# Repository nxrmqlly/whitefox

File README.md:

# whitefox :: an RP2350B devboard
> 💥 very chonky!

## What's this? ooh shiny.

whitefox is a Raspberry Pi RP2350B based **devboard** with *47 exposed GPIO, a 3x3 neopixel grid, a charging circuit and a MicroSD card reader* onboard!
Some may even say that it is *batteries included* but sorry we don't include batteries :(

## Why?

I wanted to have a go at making a devboard so I initially thought of using the RP2040 Chip but that thing is old now and very overused so here
we are with the RP2040's successor, the RP2350! Most RP2350 boards (like the Raspberry Pi Pico *2*) use the QFN-60 layout on the RP2350A chip 
and I haven't really seen devboards use the RP2350B, which is a QFN-80 chip, meaning it exposes the full power of the RP2350 in a bigger die.

## The PCB

The Schematic is a combination of very many different projects and the official and amazing
[Hardware design with RP2350](https://pip-assets.raspberrypi.com/categories/1214-rp2350/documents/RP-008280-DS-1-hardware-design-with-rp2350.pdf)
The PCB is configured in a 4 layer stackup as follows (from the top): `SIG / GND / PWR / SIG` and includes copper pours on all layers except
the PWR layer (duh.)
Most components are SMD on top of the board, only the JST connector is through hole.

The PCB exposes two 2x16 standard 2.54 mm pitch header holes on both sides and an additional 1x3 2.54mm pitch connector as a debug header.

| What                                       | Image                                |
|--------------------------------------------|--------------------------------------|
| [PCB](./Docs/whitefox-pcb.pdf)             |              |
| [Schematic](./Docs/whitefox-schematic.pdf) |  |

The PCB and Schematic are available in a high quality PDFs in [Docs/](Docs/)

## 3D stuff
| <center>Front</center>             | <center>Back</center>            |
|------------------------------------|----------------------------------|
|  |  |

## The BOM

Lazy to type it here so...

The full BOM can be found at [BOM/bom.csv](./BOM/BOM.csv)!

## Why the name?

> There are 2 hard problems in computer science: cache invalidation, **naming things**, and off-by-1 errors.
>
> *-- Leon Bambrick*

yeah that should be enough for an explanation.

## How to build / use it IRL

1. Spend some \$\$\$ get parts from the [BOM](./BOM/BOM.csv)
2. Use the gerbers from [production/gerbers.zip](production/gerbers.zip) to fabricate a PCB.
3. With some elbow grease and reference from the schematic, get to soldering the tiny SMD components
4. You're done! Go crazy

Alternatively, you can preserve your sanity and [get a PCBA service instead.](https://jlcpcb.com)
1. Gerbers are at [production/gerbers.zip](production/gerbers.zip)
2. JLCPCB BOM (not project bom!!) is at [production/jlc_bom.csv](production/jlc_bom.csv)
3. Pick and Place (CPL) file is at [production/positions.csv](production/positions.csv)

## Credits where credits are due.

Grateful for:
- [euvalennn's RPBoard^2](https://github.com/euvalennn/rpboard-squared) for a lot of design inspiration and schematic help.
- [Fallout by hackclub](https://fallout.hackclub.com/) for giving me the oppourtunity and public brand assets!
- hackclub slack for the coolest people that helped out!

## License

The hardware (PCB) is licensed under `CERN Open Hardware Licence Version 2 - Strongly Reciprocal` which means, you're all-right to copy my work and use it in yours but you must disclose your source code and project files to opensource repositories if you include part of my work in yours. See [LICENSE](LICENSE).

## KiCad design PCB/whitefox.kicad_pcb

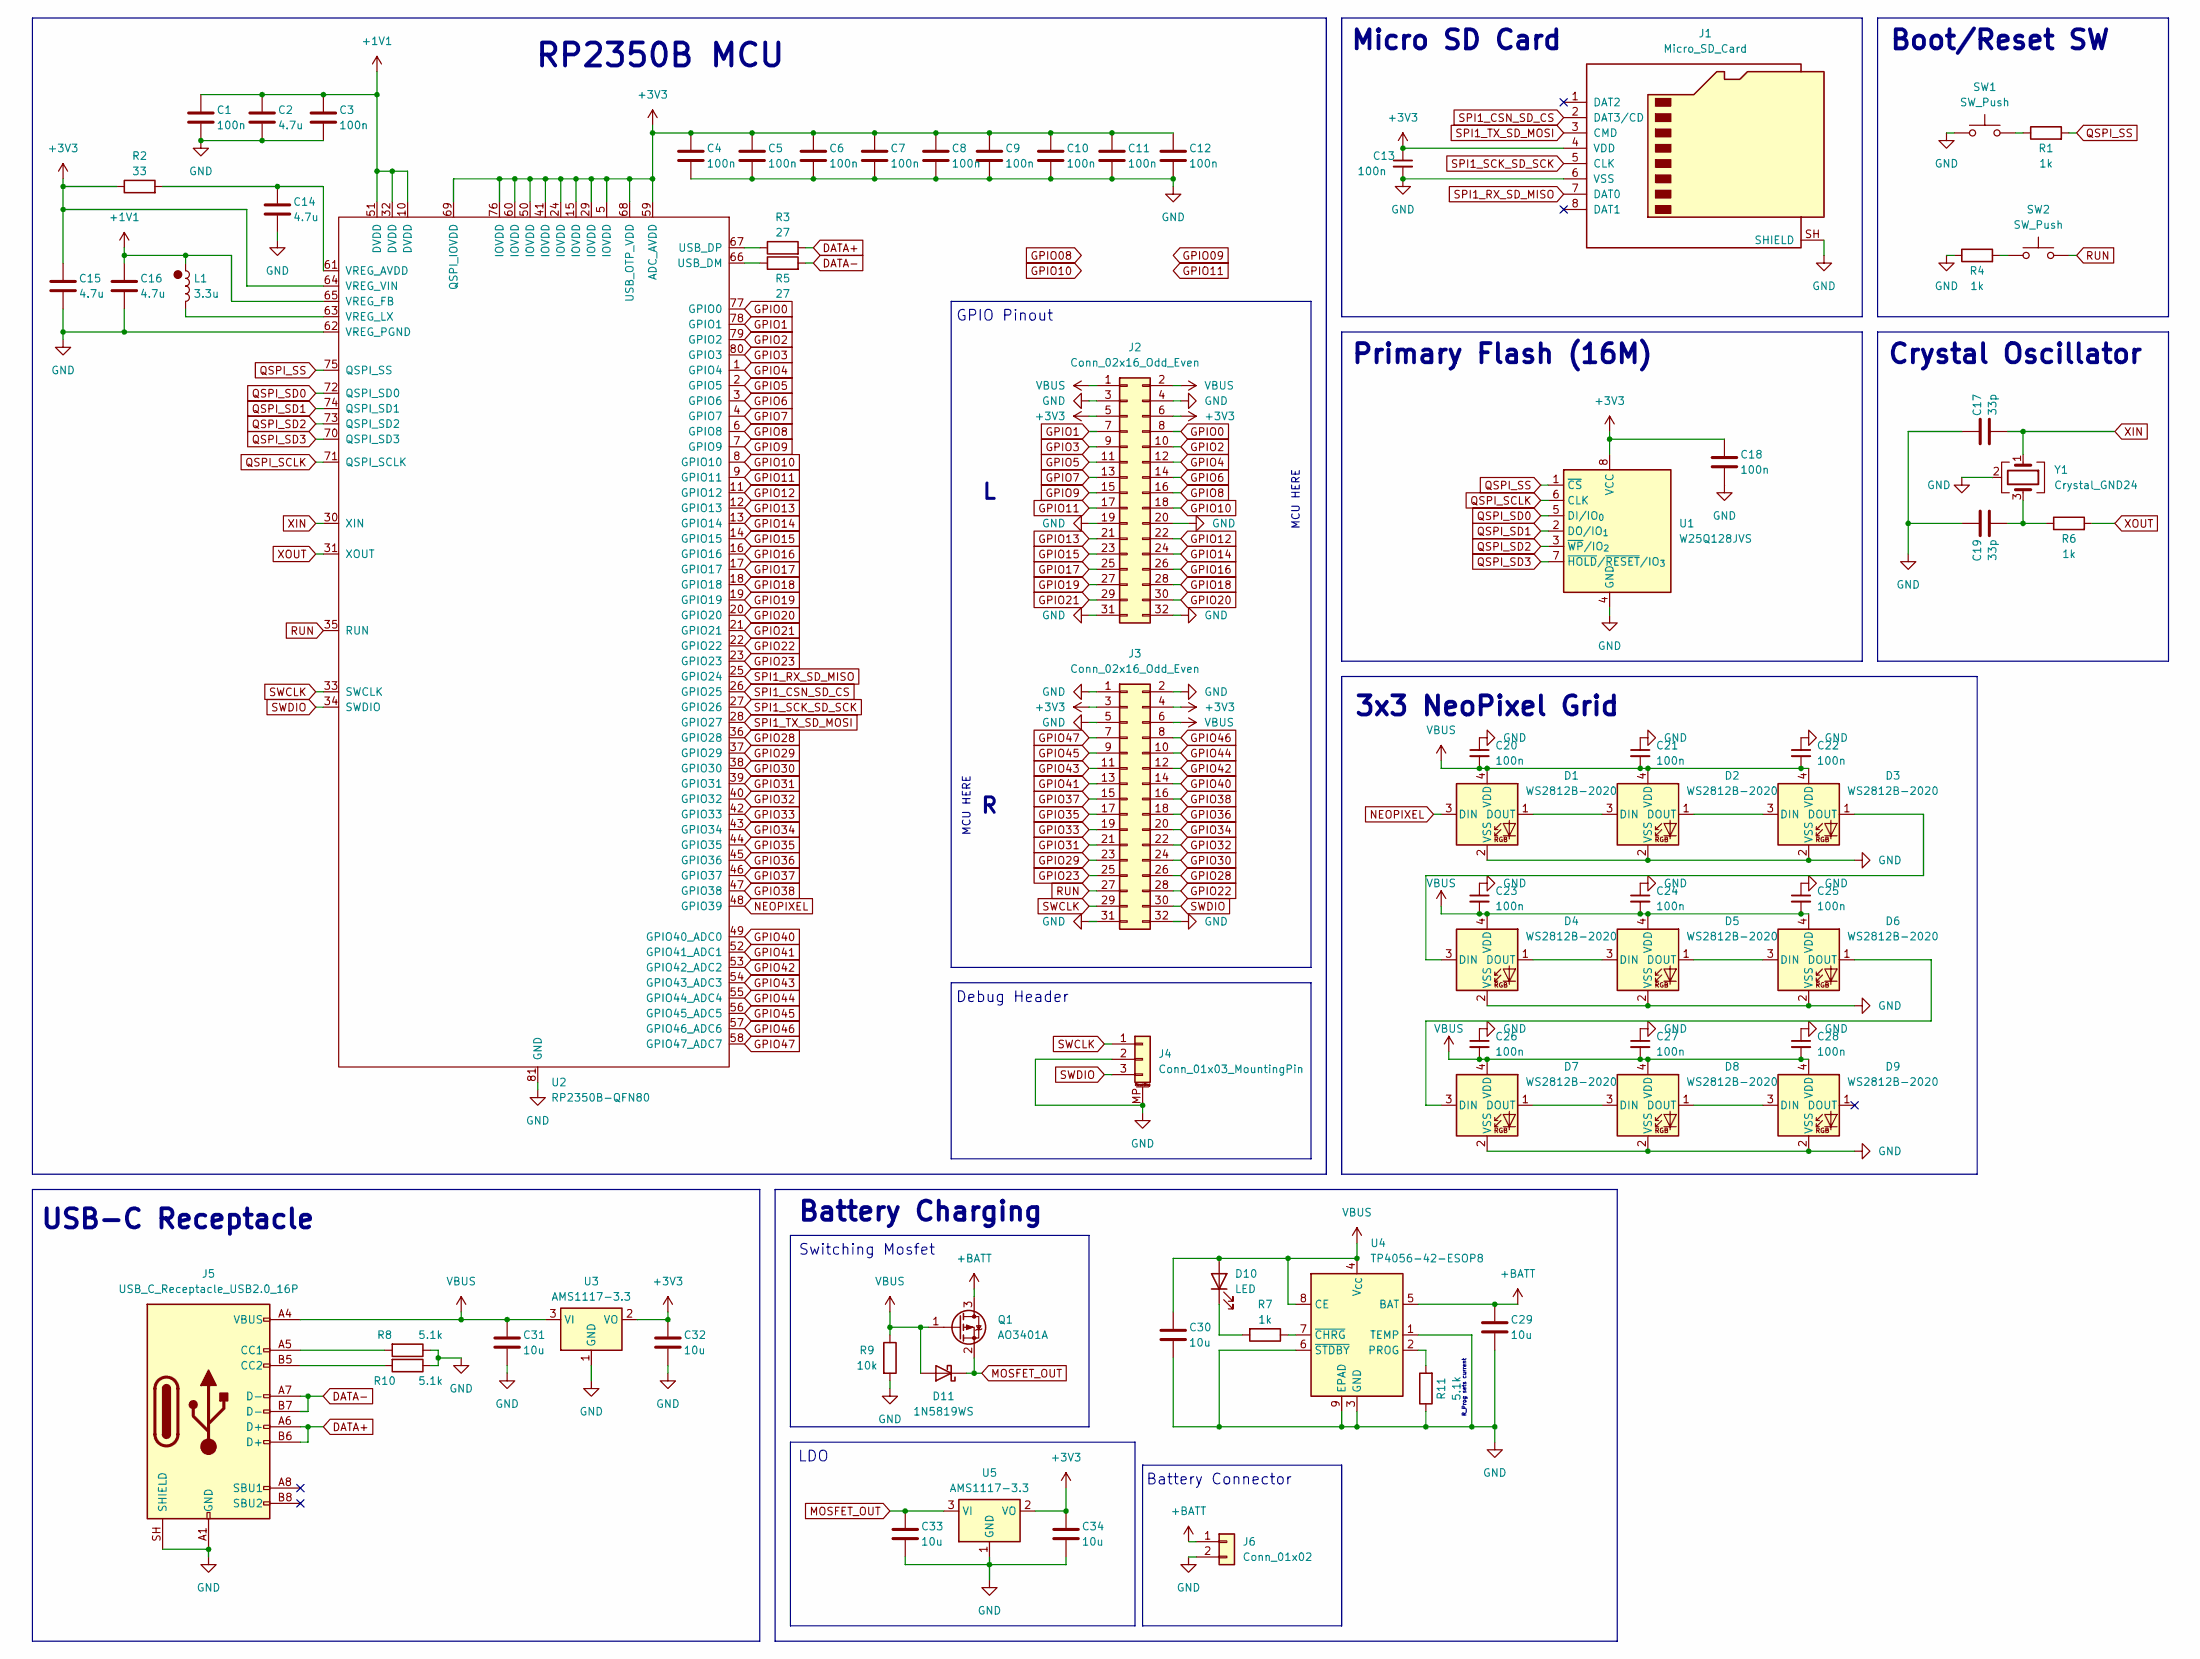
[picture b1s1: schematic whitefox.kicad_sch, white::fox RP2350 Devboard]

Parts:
C1, C3, C4, C5, C6, C7, C8, C9, C10, C11, C12, C13, C18, C20, C21, C22, C23, C24, C25, C26, C27, C28: 100n; C_0402_1005Metric
C2, C14, C15, C16: 4.7u; C_0402_1005Metric
C17, C19: 33p; C_0402_1005Metric
C29, C30, C31, C32, C33, C34: 10u; C_0402_1005Metric
D1, D2, D3, D4, D5, D6, D7, D8, D9: WS2812B-2020; LED_WS2812C-2020
D10: LED; LED_0603_1608Metric
D11: 1N5819WS; D_SOD-323
J1: Micro_SD_Card; TF-01A
J2, J3: Conn_02x16_Odd_Even; PinHeader_2x16_P2.54mm_Vertical
J4: Conn_01x03_MountingPin; PinHeader_1x03_P2.54mm_Vertical
J5: USB_C_Receptacle_USB2.0_16P; TYPE-C-31-M-12
J6: Conn_01x02; JST_PH_S2B-PH-K_1x02_P2.00mm_Horizontal
L1: 3.3u; IND-SMD_L2.0-W1.6_AOTA-B201610S3R3-101-T
Q1: AO3401A; SOT-23
R1, R4, R6, R7: 1k; R_0402_1005Metric
R2: 33; R_0402_1005Metric
R3, R5: 27; R_0402_1005Metric
R8, R10, R11: 5.1k; R_0402_1005Metric
R9: 10k; R_0402_1005Metric
SW1, SW2: SW_Push; TS-1088-ARXXX
U1: W25Q128JVS; SOIC-8_5.3x5.3mm_P1.27mm
U2: RP2350B-QFN80; QFN-80-1EP_10x10mm_P0.4mm_EP3.4x3.4mm
U3, U5: AMS1117-3.3; SOT-223-3_TabPin2
U4: TP4056-42-ESOP8; SOIC-8-1EP_3.9x4.9mm_P1.27mm_EP2.41x3.3mm_ThermalVias
Y1: Crystal_GND24; XTAL_ABM8-272-T3

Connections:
+1V1: C1.1, C2.1, C3.1, C16.2, L1.1, U2.10 (DVDD), U2.32 (DVDD), U2.51 (DVDD), U2.65 (VREG_FB)
+3V3: C4.1, C5.1, C6.1, C7.1, C8.1, C9.1, C10.1, C11.1, C12.1, C13.1, C15.1, C18.1, C32.1, C34.1, J1.4 (VDD), J2.5, J2.6, J3.3, J3.4, R2.1, U1.8 (VCC), U2.5 (IOVDD), U2.15 (IOVDD), U2.24 (IOVDD), U2.29 (IOVDD), U2.41 (IOVDD), U2.50 (IOVDD), U2.59 (ADC_AVDD), U2.60 (IOVDD), U2.64 (VREG_VIN), U2.68 (USB_OTP_VDD), U2.69 (QSPI_IOVDD), U2.76 (IOVDD), U3.2 (VO), U5.2 (VO)
+BATT: C29.1, J6.1, Q1.3 (D), U4.5 (BAT)
DATA+: J5.A6 (D+), J5.B6 (D+), R3.2
DATA-: J5.A7 (D-), J5.B7 (D-), R5.2
GND: C1.2, C2.2, C3.2, C4.2, C5.2, C6.2, C7.2, C8.2, C9.2, C10.2, C11.2, C12.2, C13.2, C14.2, C15.2, C16.1, C17.2, C18.2, C19.2, C20.1, C21.1, C22.1, C23.1, C24.1, C25.1, C26.1, C27.1, C28.1, C29.2, C30.2, C31.2, C32.2, C33.2, C34.2, D1.2 (VSS), D2.2 (VSS), D3.2 (VSS), D4.2 (VSS), D5.2 (VSS), D6.2 (VSS), D7.2 (VSS), D8.2 (VSS), D9.2 (VSS), J1.6 (VSS), J1.SH (SHIELD), J2.3, J2.4, J2.19, J2.20, J2.31, J2.32, J3.1, J3.2, J3.5, J3.31, J3.32, J4.2, J4.MP (MountPin), J5.A1 (GND), J5.A12 (GND), J5.B1 (GND), J5.B12 (GND), J5.SH (SHIELD), J6.2, R4.1, R8.1, R9.2, R10.1, R11.1, SW1.1, U1.4 (GND), U2.62 (VREG_PGND), U2.81 (GND), U3.1 (GND), U4.1 (TEMP), U4.3 (GND), U4.6 (~STDBY), U4.9 (EPAD), U5.1 (GND), Y1.2 (G), Y1.4 (G)
GPIO0: J2.8, U2.77 (GPIO0)
GPIO1: J2.7, U2.78 (GPIO1)
GPIO2: J2.10, U2.79 (GPIO2)
GPIO3: J2.9, U2.80 (GPIO3)
GPIO4: J2.12, U2.1 (GPIO4)
GPIO5: J2.11, U2.2 (GPIO5)
GPIO6: J2.14, U2.3 (GPIO6)
GPIO7: J2.13, U2.4 (GPIO7)
GPIO8: J2.16, U2.6 (GPIO8)
GPIO9: J2.15, U2.7 (GPIO9)
GPIO10: J2.18, U2.8 (GPIO10)
GPIO11: J2.17, U2.9 (GPIO11)
GPIO12: J2.22, U2.11 (GPIO12)
GPIO13: J2.21, U2.12 (GPIO13)
GPIO14: J2.24, U2.13 (GPIO14)
GPIO15: J2.23, U2.14 (GPIO15)
GPIO16: J2.26, U2.16 (GPIO16)
GPIO17: J2.25, U2.17 (GPIO17)
GPIO18: J2.28, U2.18 (GPIO18)
GPIO19: J2.27, U2.19 (GPIO19)
GPIO20: J2.30, U2.20 (GPIO20)
GPIO21: J2.29, U2.21 (GPIO21)
GPIO22: J3.28, U2.22 (GPIO22)
GPIO23: J3.25, U2.23 (GPIO23)
GPIO28: J3.26, U2.36 (GPIO28)
GPIO29: J3.23, U2.37 (GPIO29)
GPIO30: J3.24, U2.38 (GPIO30)
GPIO31: J3.21, U2.39 (GPIO31)
GPIO32: J3.22, U2.40 (GPIO32)
GPIO33: J3.19, U2.42 (GPIO33)
GPIO34: J3.20, U2.43 (GPIO34)
GPIO35: J3.17, U2.44 (GPIO35)
GPIO36: J3.18, U2.45 (GPIO36)
GPIO37: J3.15, U2.46 (GPIO37)
GPIO38: J3.16, U2.47 (GPIO38)
GPIO40: J3.14, U2.49 (GPIO40_ADC0)
GPIO41: J3.13, U2.52 (GPIO41_ADC1)
GPIO42: J3.12, U2.53 (GPIO42_ADC2)
GPIO43: J3.11, U2.54 (GPIO43_ADC3)
GPIO44: J3.10, U2.55 (GPIO44_ADC4)
GPIO45: J3.9, U2.56 (GPIO45_ADC5)
GPIO46: J3.8, U2.57 (GPIO46_ADC6)
GPIO47: J3.7, U2.58 (GPIO47_ADC7)
MOSFET_OUT: C33.1, D11.1 (K), Q1.2 (S), U5.3 (VI)
NEOPIXEL: D1.3 (DIN), U2.48 (GPIO39)
unnamed: C19.1, R6.1, Y1.3
unnamed: D1.1 (DOUT), D2.3 (DIN)
unnamed: D2.1 (DOUT), D3.3 (DIN)
unnamed: D3.1 (DOUT), D4.3 (DIN)
unnamed: D4.1 (DOUT), D5.3 (DIN)
unnamed: D5.1 (DOUT), D6.3 (DIN)
unnamed: D6.1 (DOUT), D7.3 (DIN)
unnamed: D7.1 (DOUT), D8.3 (DIN)
unnamed: D8.1 (DOUT), D9.3 (DIN)
unnamed: D10.1 (K), R7.2
unnamed: J5.A5 (CC1), R8.2
unnamed: J5.B5 (CC2), R10.2
unnamed: R1.1, SW1.2
unnamed: R4.2, SW2.1
unnamed: R5.1, U2.66 (USB_DM)
unnamed: R3.1, U2.67 (USB_DP)
unnamed: C14.1, R2.2, U2.61 (VREG_AVDD)
unnamed: L1.2, U2.63 (VREG_LX)
unnamed: R11.2, U4.2 (PROG)
unnamed: R7.1, U4.7 (~CHRG)
QSPI_SCLK: U1.6 (CLK), U2.71 (QSPI_SCLK)
QSPI_SD0: U1.5 (DI/IO_{0}), U2.72 (QSPI_SD0)
QSPI_SD1: U1.2 (DO/IO_{1}), U2.74 (QSPI_SD1)
QSPI_SD2: U1.3 (~WP/IO_{2}), U2.73 (QSPI_SD2)
QSPI_SD3: U1.7 (~HOLD/~RESET/IO_{3}), U2.70 (QSPI_SD3)
QSPI_SS: R1.2, U1.1 (~CS), U2.75 (QSPI_SS)
RUN: J3.27, SW2.2, U2.35 (RUN)
SPI1_CSN_SD_CS: J1.2 (DAT3/CD), U2.26 (GPIO25)
SPI1_RX_SD_MISO: J1.7 (DAT0), U2.25 (GPIO24)
SPI1_SCK_SD_SCK: J1.5 (CLK), U2.27 (GPIO26)
SPI1_TX_SD_MOSI: J1.3 (CMD), U2.28 (GPIO27)
SWCLK: J3.29, J4.1, U2.33 (SWCLK)
SWDIO: J3.30, J4.3, U2.34 (SWDIO)
VBUS: C20.2, C21.2, C22.2, C23.2, C24.2, C25.2, C26.2, C27.2, C28.2, C30.1, C31.1, D1.4 (VDD), D2.4 (VDD), D3.4 (VDD), D4.4 (VDD), D5.4 (VDD), D6.4 (VDD), D7.4 (VDD), D8.4 (VDD), D9.4 (VDD), D10.2 (A), D11.2 (A), J2.1, J2.2, J3.6, J5.A4 (VBUS), J5.A9 (VBUS), J5.B4 (VBUS), J5.B9 (VBUS), Q1.1 (G), R9.1, U3.3 (VI), U4.4 (V_{CC}), U4.8 (CE)
XIN: C17.1, U2.30 (XIN), Y1.1
XOUT: R6.2, U2.31 (XOUT)

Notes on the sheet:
RP2350B MCU
MCU HERE
Battery Charging
LDO
Debug Header
USB-C Receptacle
Switching Mosfet
Boot/Reset SW
R_Prog sets current
Crystal Oscillator
3x3 NeoPixel Grid
Battery Connector
GPIO Pinout
Primary Flash (16M)
Micro SD Card

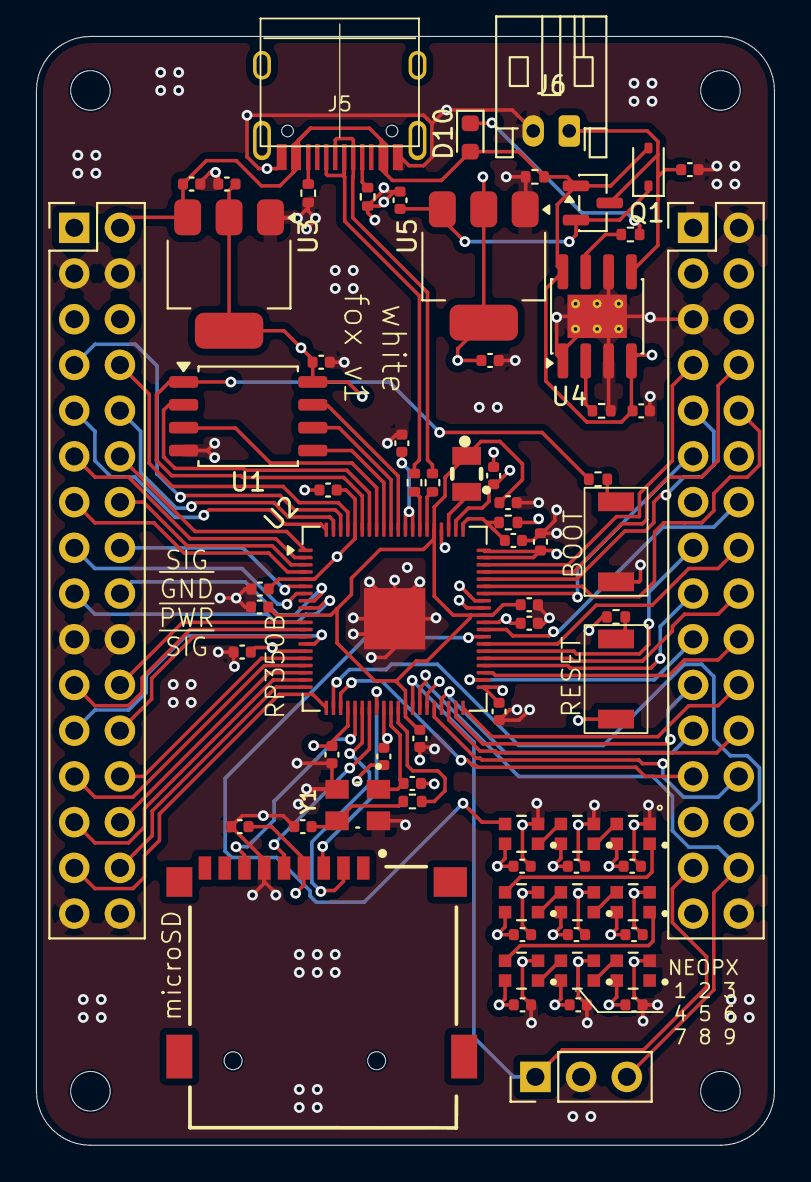
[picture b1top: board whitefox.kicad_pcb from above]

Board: 4 copper layers, 41.0 x 61.6 mm, 72 parts (0 on the bottom side), 87 nets.

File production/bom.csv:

Designator,Footprint,Quantity,Value,LCSC Part #
"C1, C10, C11, C12, C13, C17, C3, C4, C5, C6, C7, C8, C9",0402,13,100n,C1525
"C14, C15, C16, C2",0402,4,4.7u,C23733
"C18, C19",0402,2,33p,C1562
"C20, C21, C22, C23, C24, C25",0402,6,10u,C15525
"D1, D10, D11, D2, D3, D4, D5, D6, D9",LED_WS2812C-2020,9,WS2812B-2020,C2976072
D7,0603,1,LED,C2286
D8,D_SOD-323,1,1N5819WS,C191023
J1,TF-01A,1,Micro_SD_Card,C91145
"J2, J3",PinHeader_2x16_P2.54mm_Vertical,2,Conn_02x16_Odd_Even,
J4,PinHeader_1x03_P2.54mm_Vertical,1,Conn_01x03_MountingPin,
J5,TYPE-C-31-M-12,1,USB_C_Receptacle_USB2.0_16P,C165948
J6,JST_PH_S2B-PH-K_1x02_P2.00mm_Horizontal,1,Conn_01x02,C173752
L1,0805,1,3.3u,C42411119
Q1,SOT-23,1,AO3401A,C15127
"R1, R4, R6, R7",0402,4,1k,C11702
"R10, R11, R8",0402,3,5.1k,C25905
R2,0402,1,33,C25105
"R3, R5",0402,2,27,C25100
R9,0402,1,10k,C25744
"SW1, SW2",TS-1088-ARXXX,2,SW_Push,C720477
U1,SOIC-8_5.3x5.3mm_P1.27mm,1,W25Q128JVS,C97521
U2,QFN-80-1EP_10x10mm_P0.4mm_EP3.4x3.4mm,1,RP2350B-QFN80,C42415655
"U3, U5",SOT-223-3_TabPin2,2,AMS1117-3.3,C6186
U4,SOIC-8-1EP_3.9x4.9mm_P1.27mm_EP2.41x3.3mm_ThermalVias,1,TP4056-42-ESOP8,C16581
Y1,XTAL_ABM8-272-T3,1,Crystal_GND24,C9002

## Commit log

2026-04-29 Polish everything to repo
2026-04-29 upload to github
2026-05-02 add decoupling caps
